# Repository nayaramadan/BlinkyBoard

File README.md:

# BlinkyBoard
KiCad Blinky Board in the shape of a diamond!
There is also a drawn heart in the PCB to add a small personal touch to it.

BOM:

<<<<<<< HEAD

Here's the BOM with components (also named BOMwithcomponents in the git)

=======

 This is a cool blinky board I made inspired by the stars!! It features a star shape along with a mini cut out heart. I started to build my first PCB, and definitely learned that! I leearned so much about KiCad, even from a simple project like this; I learned about footprints, schematics vs. pcb, and how to wire on a board! I loved making this project, it taught me a lot of the fundamentals for KiCad and I'm excited to build it

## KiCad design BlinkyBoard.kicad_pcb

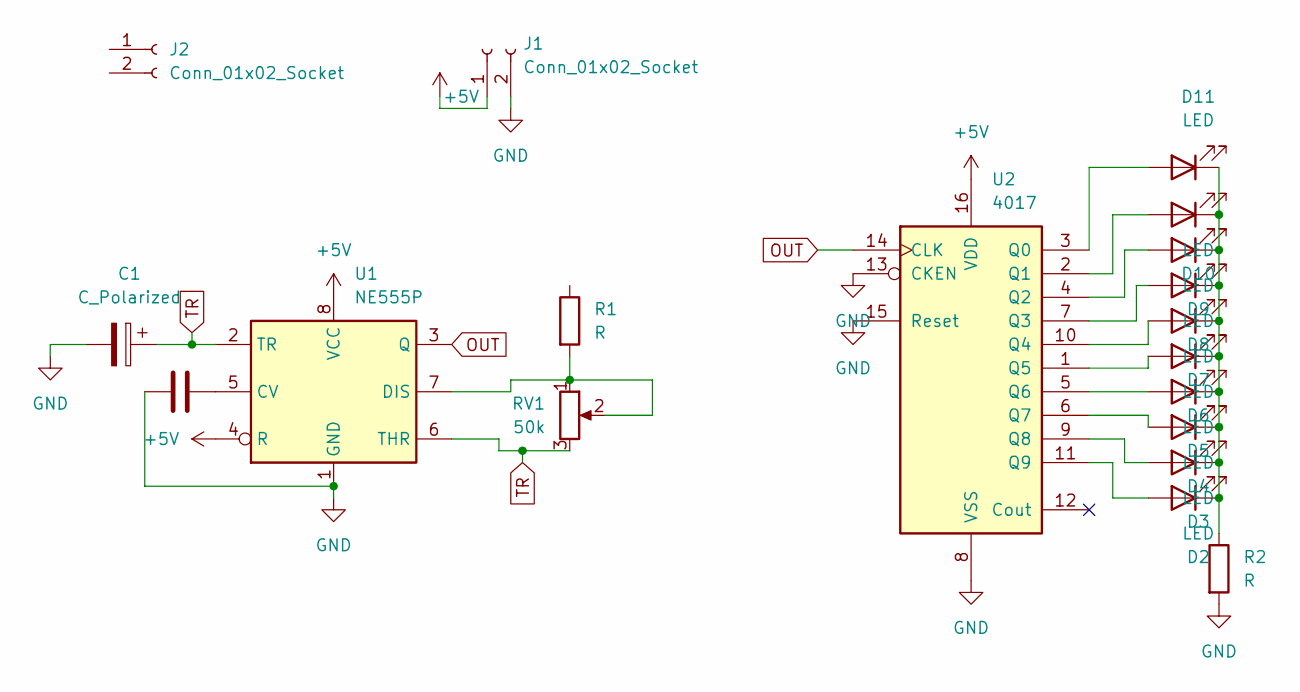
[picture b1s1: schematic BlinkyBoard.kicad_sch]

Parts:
C1: C_Polarized; CP_Radial_D5.0mm_P2.00mm
C2: C; C_Disc_D7.5mm_W2.5mm_P5.00mm
D2, D3, D4, D5, D6, D7, D8, D9, D10, D11: LED; LED_D3.0mm
J1, J2: Conn_01x02_Socket; PinHeader_1x02_P2.54mm_Vertical
R1, R2: R; R_Axial_DIN0207_L6.3mm_D2.5mm_P7.62mm_Horizontal
RV1: 50k; Potentiometer_Vishay_T93YA_Vertical
U1: NE555P; DIP-8_W7.62mm
U2: 4017; N16

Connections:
+5V: J1.1, U1.4 (R), U1.8 (VCC), U2.16 (VDD)
/<NO NET>: R1.1
GND: C1.2, C2.1, J1.2, R2.2, U1.1 (GND), U2.8 (VSS), U2.13 (CKEN), U2.15 (Reset)
unnamed: D2.2 (A), U2.11 (Q9)
unnamed: D3.2 (A), U2.9 (Q8)
unnamed: D4.2 (A), U2.6 (Q7)
unnamed: D5.2 (A), U2.5 (Q6)
unnamed: D6.2 (A), U2.1 (Q5)
unnamed: D7.2 (A), U2.10 (Q4)
unnamed: D8.2 (A), U2.7 (Q3)
unnamed: D9.2 (A), U2.4 (Q2)
unnamed: D10.2 (A), U2.2 (Q1)
unnamed: D2.1 (K), D3.1 (K), D4.1 (K), D5.1 (K), D6.1 (K), D7.1 (K), D8.1 (K), D9.1 (K), D10.1 (K), D11.1 (K), R2.1
unnamed: D11.2 (A), U2.3 (Q0)
unnamed: C2.2, U1.5 (CV)
unnamed: R1.2, RV1.1, RV1.2, U1.7 (DIS)
OUT: U1.3 (Q), U2.14 (CLK)
TR: C1.1, RV1.3, U1.2 (TR), U1.6 (THR)

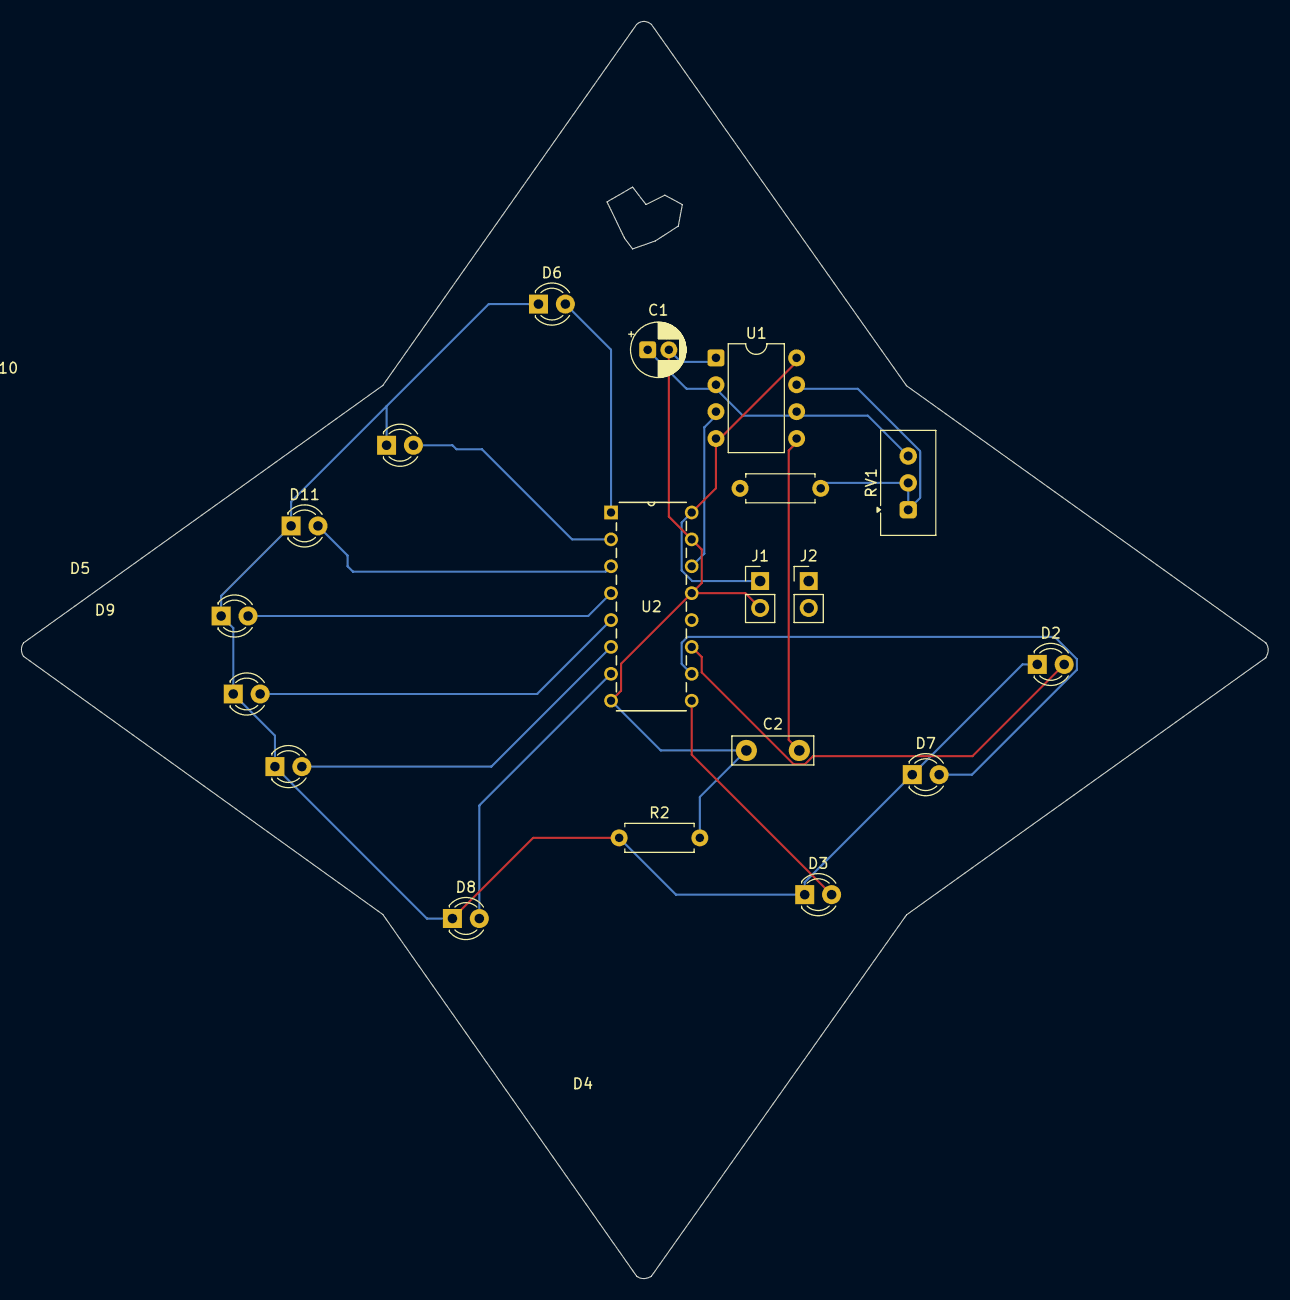
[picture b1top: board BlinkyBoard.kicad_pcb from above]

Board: 2 copper layers, 117.8 x 118.7 mm, 19 parts (0 on the bottom side), 17 nets.

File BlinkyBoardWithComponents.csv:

"Qty","Value","DNP","Exclude from BOM","Exclude from Board","Footprint","#"
"1","C_Polarized","","","","Capacitor_THT:CP_Radial_D5.0mm_P2.00mm","1"
"1","C","","","","Capacitor_THT:C_Disc_D7.5mm_W2.5mm_P5.00mm","2"
"10","LED","","","","LED_THT:LED_D3.0mm","3"
"2","Conn_01x02_Socket","","","","Connector_PinHeader_2.54mm:PinHeader_1x02_P2.54mm_Vertical","4"
"2","R","","","","Resistor_THT:R_Axial_DIN0207_L6.3mm_D2.5mm_P7.62mm_Horizontal","5"
"1","50k","","","","Potentiometer_THT:Potentiometer_Vishay_T93YA_Vertical","6"
"1","NE555P","","","","Package_DIP:DIP-8_W7.62mm","7"
"1","4017","","","","footprints:N16","8"

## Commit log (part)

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2026-04-12 kicad stuff
2026-06-02 Enhance README with board shape and design details
    Added a description of the board's shape and design.
2026-06-02 Add image to README for BlinkyBoard project
2026-06-02 Forgot to upload my gerber file as a zip! Reuploaded
2026-06-24 Revert "Initial commit"
    This reverts commit e504e2252d0adfb80bc8437220d008c6d6f3c1aa.
2026-06-24 gonna reupload my files
2026-06-24 changed readme pic
2026-06-26 final edits!
2026-06-26 Enhance README with project details and insights
    Added project description and personal insights about learning KiCad.
